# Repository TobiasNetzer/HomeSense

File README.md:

# HomeSense - IoT Environmental Sensor 

ESP32-C3 based IoT Temperature, Humidity, Air Quality and Air Pressure Sensor with logging capabilities. 

Initially, the idea was simply to monitor temperature and humidity wirelessly. Along the way, I chose the Bosch BME680 sensor, which also provides air pressure and air quality measurements.

Sensor data is primarily transmitted via MQTT. To ensure continued operation in the absence of Wi-Fi, the device also supports local data logging using a microSD card and includes a real-time clock (RTC) for accurate timestamps.

When considering the form factor I thought about using one of the pre-made ESP32-C3 modules. While that would have streamlined the design, I wanted the board to be as small as possible, so I went with a fully custom design.

The case fits a 250mAh battery and also embeds a small magnet in the back lid to allow it to be mounted on magnetic surfaces. I put in a small light pipe for the RGB-LED, a few ventilation holes/slots for the BME680 and a cutout for the microSD card.
Fully assembled it measures 15x25x35mm.

Take a look at the design documents for more info:
- [Schematic](docs/Schematic.pdf)
- [Assembly Drawing](docs/HomeSense%20Assembly%20Drawing.pdf)
- [BOM](https://htmlpreview.github.io/?https://github.com/TobiasNetzer/HomeSense/blob/main/docs/BOM.html)

# Data Acquisition 📊

Bosch supplies an API for the BME680 which can be used to get raw values from the sensor. This is good enough if you only want temperature and humidity for example. But the sensor is capable of quite a bit more, like providing indoor air quality levels. For this, the additional BSEC (Bosch Sensortec Environmental Cluster) software is needed. This library takes care of all the sensor fusion and provides ambient air temperature, ambient relative humidity, air pressure and indoor air quality (IAQ).

To configure the device, I made a super basic webpage, which is hosted by the ESP32. This allows setting up the Wi-Fi connection and MQTT. There is a lot to be added, but for initial testing this works fine.

Once everything is setup, a JSON string containing all the sensor data can be received every 15min by subscribing to the configured MQTT topic. 

Here is an example of the data:

```json
{
   "timestamp":"2023-07-15T13:03",
   "temperature":{
      "value":27.33,
      "unit":"Celsius"
   },
   "humidity":{
      "value":38.87,
      "unit":"percent"
   },
   "pressure":{
      "value":94787.31,
      "unit":"Pa"
   },
   "gas_resistance":{
      "value":211406.42,
      "unit":"Ohm"
   },
   "iaq":79.60,
   "iaq_accuracy":3,
   "static_iaq":79.18,
   "static_iaq_accuracy":3,
   "co2_equivalent":{
      "value":791.80,
      "unit":"ppm"
   },
   "breath_voc_equivalent":{
      "value":0.97,
      "unit":"ppm"
   },
   "gas_percentage":{
      "value":21.45,
      "unit":"percent"
   },
   "run_in_status":1,
   "stabilization_status":1,
   "battery_voltage":{
      "value":3868,
      "unit":"mV"
   }
}
```

# Issues

Unfortunately the thermal isolation cutouts around the BME680 aren't as effective as I had hoped. When the ESP32 is running continuously, like when the webserver for configuration is running, the temperature reading of the BME680 increases by around 3°C. Ofc the small footprint of the board also doesn't help, since there is very little distance between the ESP and the sensor.

Even though the cutouts seem to help a bit and the ground plane was removed below the sensor area, the bridge for the power and data lines provides a direct path for the heat. A complete U-shape would have probably been a much more effective design choice.

In order to avoid reporting false temperature and humidity data, the ESP has to be in sleep mode for some time to allow the board to cool down before taking another reading from the sensor.

This also applies while charging the battery. Currently the charge current is configured for 50mA, but this is still enough to increase the temperature readings by a small amount.

The workaround for now is to wait around 10min after the webserver is shut off, before taking the first reading and also disable any readings while charging. This isn't a huge problem, since data is only transmitted every 15min.

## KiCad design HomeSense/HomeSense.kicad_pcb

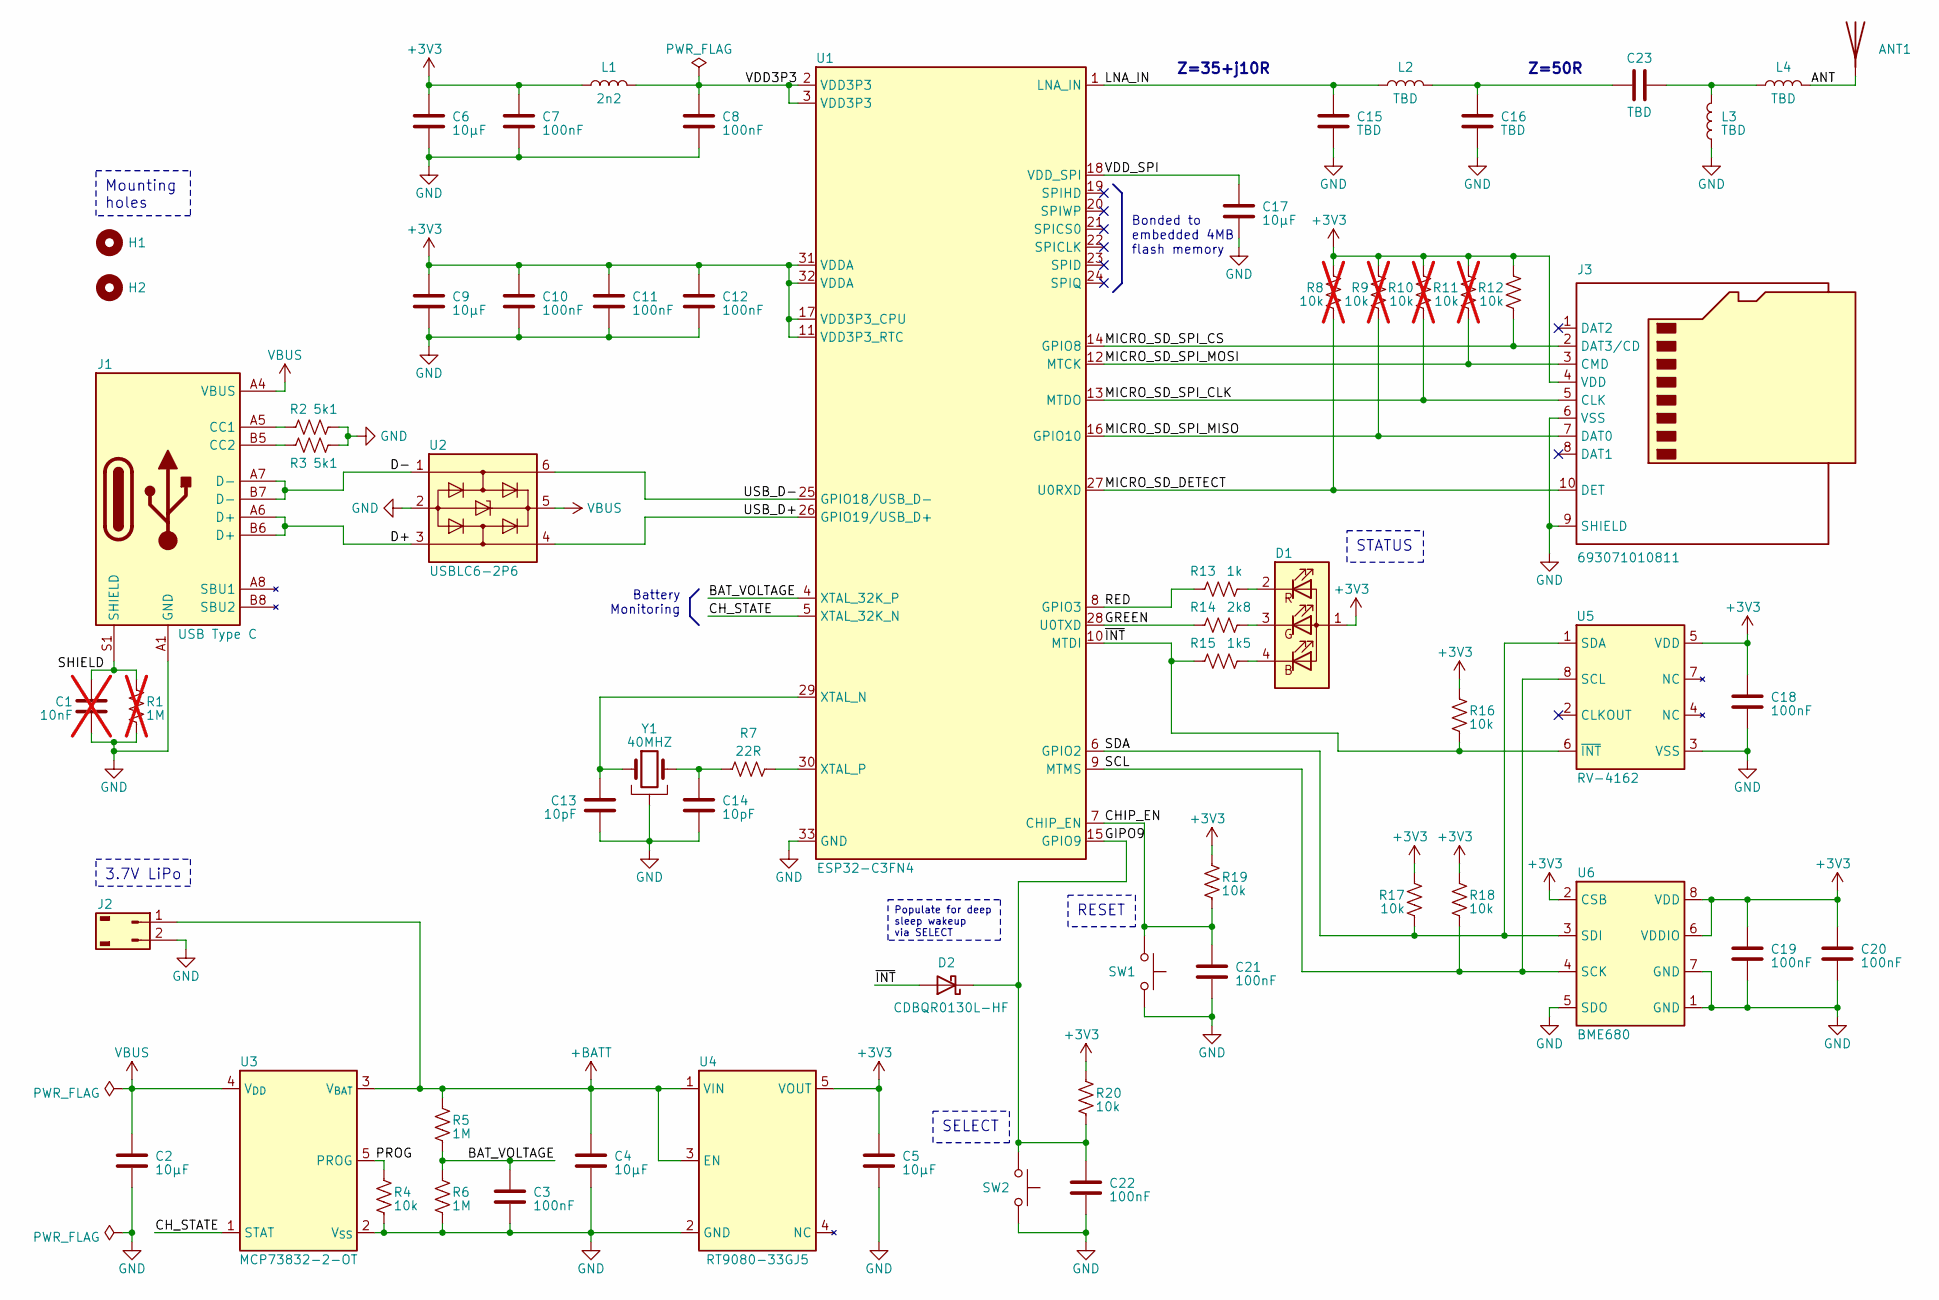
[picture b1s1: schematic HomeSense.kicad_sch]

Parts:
ANT1: 2450AT18B100E; Johanson_2450AT18x100; Manufacturer Part Number 2450AT18B100E
C1: 10nF; C_0402_(1005_Metric); Manufacturer Part Number C0402C103K5RAC7411; not fitted
C2, C4, C5, C6, C9, C17: 10µF; C_0805_(2012_Metric); Manufacturer Part Number C0805C106K3PAC7800
C3, C7, C8, C10, C11, C12, C18, C19, C20, C21, C22: 100nF; C_0402_(1005_Metric); Manufacturer Part Number C0402C104K3PAC7867
C13, C14: 10pF; C_0402_(1005_Metric); Manufacturer Part Number C0402C100J3GAC7867
C15, C16, C23: TBD; C_0402_(1005_Metric)
D1: Wuerth_150044M155260; LED_0404; Manufacturer Part Number 150044M155260
D2: CDBQR0130L-HF; D_0402_(1005_Metric); Manufacturer Part Number CDBQR0130L-HF
H1, H2: MountingHole; Mounting_Hole
J1: USB Type C; USB_C_Receptacle_HRO_TYPE-C-31-M-12; Manufacturer Part Number USB_C_Receptacle_HRO_TYPE-C-31-M-12
J2: 781710002; Molex_Pico-EZmate_78171-0002_1x02-1MP_P1.20mm_Vertical; Manufacturer Part Number 781710002
J3: 693071010811; Manufacturer Part Number 693071010811
L1: 2n2; L_0402_(1005_Metric); Manufacturer Part Number LQG15WH2N2S02D
L2, L3, L4: TBD; L_0402_(1005_Metric)
R1: 1M; R_0402_(1005_Metric); Manufacturer Part Number RC0402FR-071ML; not fitted
R2, R3: 5k1; R_0402_(1005_Metric); Manufacturer Part Number RC0402FR-075K1L
R4, R12, R16, R17, R18, R19, R20: 10k; R_0402_(1005_Metric); Manufacturer Part Number RC0402FR-0710KP
R5, R6: 1M; R_0402_(1005_Metric); Manufacturer Part Number RC0402FR-071ML
R7: 22R; R_0402_(1005_Metric); Manufacturer Part Number RC0402FR-0722RP
R8, R9, R10, R11: 10k; R_0402_(1005_Metric); Manufacturer Part Number RC0402FR-0710KP; not fitted
R13: 1k; R_0402_(1005_Metric); Manufacturer Part Number AC0402FR-131KL
R14: 2k8; R_0402_(1005_Metric); Manufacturer Part Number RC0402FR-072K8L
R15: 1k5; R_0402_(1005_Metric); Manufacturer Part Number RC0402FR-071K5L
SW1, SW2: SW_Push; Button_3.2mm_4.2mm; Manufacturer Part Number PTS810SJG250SMTRLFS
U1: ESP32-C3FN4; QFN32_5x5; Manufacturer Part Number ESP32-C3FN4
U2: USBLC6-2P6; SOT-666; Manufacturer Part Number USBLC6-2P6
U3: MCP73832-2-OT; SOT-23-5; Manufacturer Part Number MCP73832T-2DCI/OT
U4: RT9080-33GJ5; SOT-23-5; Manufacturer Part Number RT9080-33GJ5
U5: RV-4162; LCC8; Manufacturer Part Number RV-4162-C7-32.768KHZ-20PPM-TA-QC
U6: BME680; Bosch_LGA-8_3x3mm_P0.8mm; Manufacturer Part Number BME680
Y1: 40MHZ; Crystal_SMD_Abracon_ABM8G-4Pin_3.2x2.5mm; Manufacturer Part Number ABM8-40.000MHZ-10-1-U-T

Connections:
+3V3: C5.1, C6.1, C7.1, C9.1, C10.1, C11.1, C12.1, C18.1, C19.1, C20.1, D1.1 (A), J3.4 (VDD), L1.1, R8.1, R9.1, R10.1, R11.1, R12.1, R16.1, R17.1, R18.1, R19.1, R20.1, U1.11 (VDD3P3_RTC), U1.17 (VDD3P3_CPU), U1.31 (VDDA), U1.32 (VDDA), U4.5 (VOUT), U5.5 (VDD), U6.2 (CSB), U6.6 (VDDIO), U6.8 (VDD)
+BATT: C4.1, J2.1, R5.1, U3.3 (V_{BAT}), U4.1 (VIN), U4.3 (EN)
/ANT: ANT1.1 (A), L4.2
/BAT_VOLTAGE: C3.1, R5.2, R6.1, U1.4 (XTAL_32K_P)
/CHIP_EN: C21.1, R19.2, SW1.1, U1.7 (CHIP_EN)
/CH_STATE: U1.5 (XTAL_32K_N), U3.1 (STAT)
/D+: J1.A6 (D+), J1.B6 (D+), U2.3 (I/O2)
/D-: J1.A7 (D-), J1.B7 (D-), U2.1 (I/O1)
/GIPO9: C22.1, D2.1 (K), R20.2, SW2.1, U1.15 (GPIO9)
/GREEN: R14.1, U1.28 (U0TXD)
/LNA_IN: C15.1, L2.1, U1.1 (LNA_IN)
/MICRO_SD_DETECT: J3.10 (DET), R8.2, U1.27 (U0RXD)
/MICRO_SD_SPI_CLK: J3.5 (CLK), R10.2, U1.13 (MTDO)
/MICRO_SD_SPI_CS: J3.2 (DAT3/CD), R12.2, U1.14 (GPIO8)
/MICRO_SD_SPI_MISO: J3.7 (DAT0), R9.2, U1.16 (GPIO10)
/MICRO_SD_SPI_MOSI: J3.3 (CMD), R11.2, U1.12 (MTCK)
/PROG: R4.1, U3.5 (PROG)
/RED: R13.1, U1.8 (GPIO3)
/SCL: R18.2, U1.9 (MTMS), U5.8 (SCL), U6.4 (SCK)
/SDA: R17.2, U1.6 (GPIO2), U5.1 (SDA), U6.3 (SDI)
/SHIELD: C1.1, J1.S1 (SHIELD), R1.1
/USB_D+: U1.26 (GPIO19/USB_D+), U2.4 (I/O2)
/USB_D-: U1.25 (GPIO18/USB_D-), U2.6 (I/O1)
/VDD3P3: C8.1, L1.2, U1.2 (VDD3P3), U1.3 (VDD3P3)
/VDD_SPI: C17.1, U1.18 (VDD_SPI)
/~INT: D2.2 (A), R15.1, R16.2, U1.10 (MTDI), U5.6 (~INT)
GND: C1.2, C2.2, C3.2, C4.2, C5.2, C6.2, C7.2, C8.2, C9.2, C10.2, C11.2, C12.2, C13.2, C14.2, C15.2, C16.2, C17.2, C18.2, C19.2, C20.2, C21.2, C22.2, J1.A1 (GND), J1.A12 (GND), J1.B1 (GND), J1.B12 (GND), J2.2, J3.6 (VSS), J3.9 (SHIELD), L3.1, R1.2, R2.2, R3.2, R4.2, R6.2, SW1.2, SW2.2, U1.33 (GND), U2.2 (GND), U3.2 (V_{SS}), U4.2 (GND), U5.3 (VSS), U6.1 (GND), U6.5 (SDO), U6.7 (GND), Y1.2, Y1.4
unnamed: C14.1, R7.1, Y1.3
unnamed: C16.1, C23.1, L2.2
unnamed: C23.2, L3.2, L4.1
unnamed: D1.4 (BK), R15.2
unnamed: D1.3 (GK), R14.2
unnamed: D1.2 (RK), R13.2
unnamed: J1.A5 (CC1), R2.1
unnamed: J1.B5 (CC2), R3.1
unnamed: C13.1, U1.29 (XTAL_N), Y1.1
unnamed: R7.2, U1.30 (XTAL_P)
VBUS: C2.1, J1.A4 (VBUS), J1.A9 (VBUS), J1.B4 (VBUS), J1.B9 (VBUS), U2.5 (VBUS), U3.4 (V_{DD})

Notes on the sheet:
Z=35+j10R
Z=50R
Battery Monitoring
Bonded to embedded 4MB flash memory
STATUS
SELECT
Mounting holes
RESET
Populate for deep sleep wakeup via SELECT
3.7V LiPo

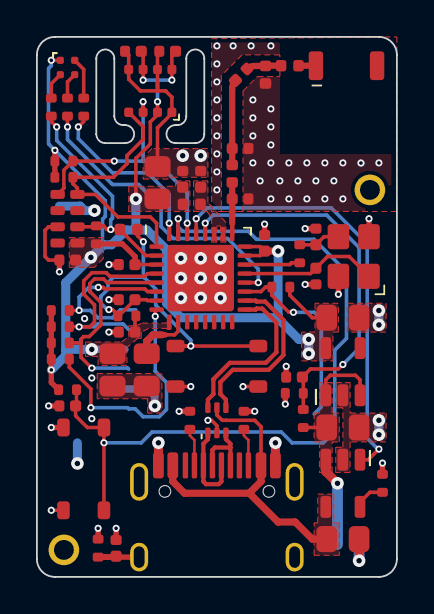
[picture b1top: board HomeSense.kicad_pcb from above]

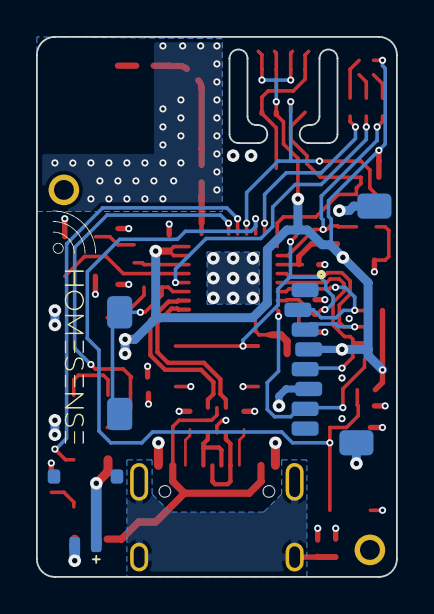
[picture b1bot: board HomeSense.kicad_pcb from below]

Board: 4 copper layers, 20.0 x 30.0 mm, 64 parts (2 on the bottom side), 38 nets.

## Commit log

2025-08-09 add case render
2025-08-10 add BOM
